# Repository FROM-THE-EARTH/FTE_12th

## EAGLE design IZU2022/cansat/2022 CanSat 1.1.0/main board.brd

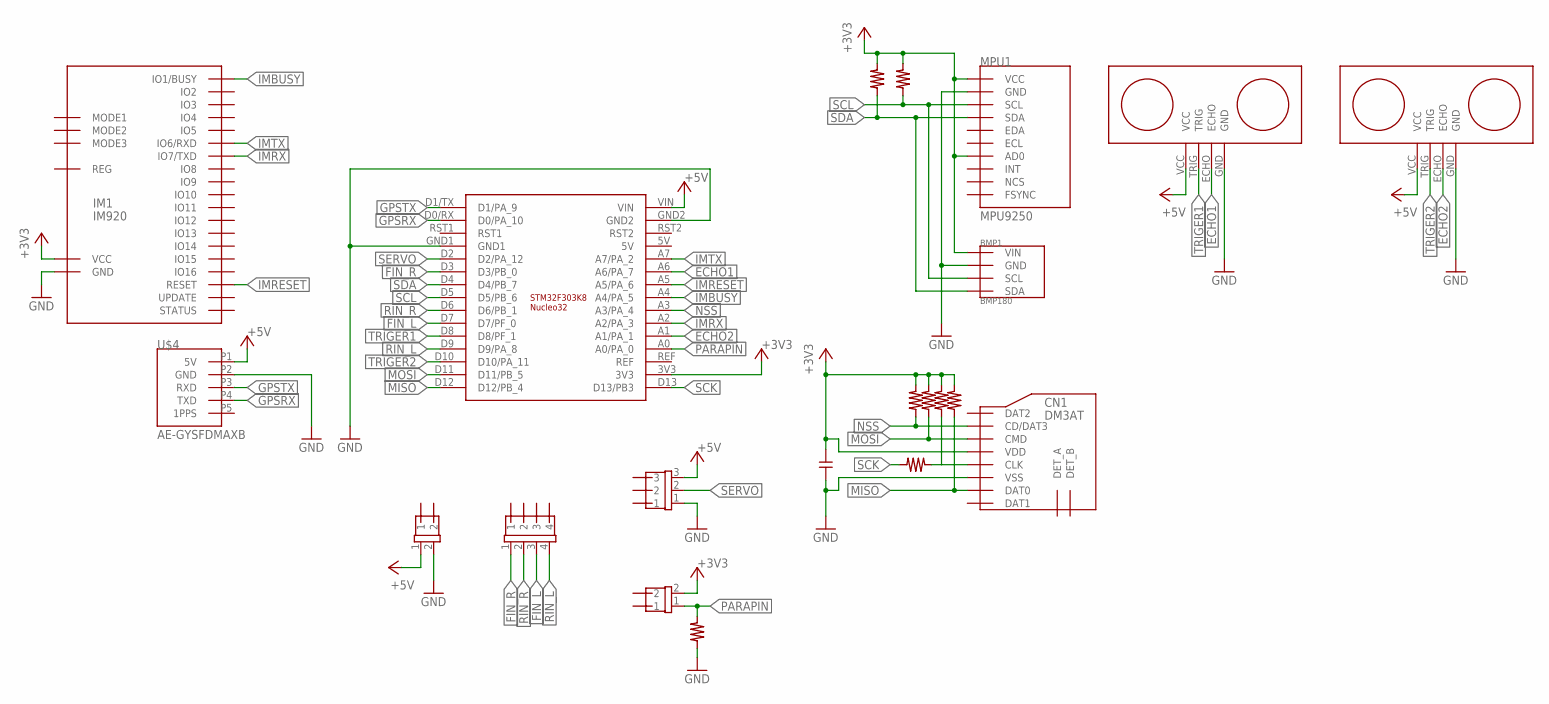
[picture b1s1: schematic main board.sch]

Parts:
BMP1: BMP180; GY-68
C4: CAPACITOR-CERAMICC_1
CN1: DM3AT
CONN1, CONN2: 2PIN
CONN3: 4PIN
CONN4: 3PIN
CP1: STM32F303K8-NUCLEO32; STM32-NUCLEO32
EC1, EC2: ECHO
IM1: IM920
MPU1: MPU9250; GY-9250
R2, R4, R5, R6, R7, R8, R9, R10: RESISTER; REGISTER
U$4: AE-GYSFDMAXB

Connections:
+3V3: BMP1.P1 (VIN), C4.2, CN1.VDD, CONN1.2, CP1.3V3, IM1.IO23 (VCC), MPU1.P1 (VCC), MPU1.P7 (AD0), R4.B, R5.B, R6.B, R7.B, R8.B, R9.B
+5V: CONN2.1, CONN4.3, CP1.VIN, EC1.VCC, EC2.VCC, U$4.P1 (5V)
ECHO1: CP1.A6 (A6/PA_7), EC1.ECHO
ECHO2: CP1.A1 (A1/PA_1), EC2.ECHO
FIN_L: CONN3.3, CP1.D7 (D7/PF_0)
FIN_R: CONN3.1, CP1.D3 (D3/PB_0)
GND: BMP1.P2 (GND), C4.1, CN1.VSS, CONN2.2, CONN4.1, CP1.GND1, CP1.GND2, EC1.GND, EC2.GND, IM1.IO24 (GND), MPU1.P2 (GND), R2.A, U$4.P2 (GND)
GPSRX: CP1.D0/RX (D0/PA_10), U$4.P4 (TXD)
GPSTX: CP1.D1/TX (D1/PA_9), U$4.P3 (RXD)
IMBUSY: CP1.A4 (A4/PA_5), IM1.IO1 (IO1/BUSY)
IMRESET: CP1.A5 (A5/PA_6), IM1.IO25 (RESET)
IMRX: CP1.A2 (A2/PA_3), IM1.IO7 (IO7/TXD)
IMTX: CP1.A7 (A7/PA_2), IM1.IO6 (IO6/RXD)
MISO: CN1.DAT0, CP1.D12 (D12/PB_4), R6.A
MOSI: CN1.CMD, CP1.D11 (D11/PB_5), R8.A
unnamed: CN1.CLK, R7.A, R10.B
NSS: CN1.CD/DAT3, CP1.A3 (A3/PA_4), R9.A
PARAPIN: CONN1.1, CP1.A0 (A0/PA_0), R2.B
RIN_L: CONN3.4, CP1.D9 (D9/PA_8)
RIN_R: CONN3.2, CP1.D6 (D6/PB_1)
SCK: CP1.D13 (D13/PB3), R10.A
SCL: BMP1.P3 (SCL), CP1.D5 (D5/PB_6), MPU1.P3 (SCL), R4.A
SDA: BMP1.P4 (SDA), CP1.D4 (D4/PB_7), MPU1.P4 (SDA), R5.A
SERVO: CONN4.2, CP1.D2 (D2/PA_12)
TRIGER1: CP1.D8 (D8/PF_1), EC1.TRIG
TRIGER2: CP1.D10 (D10/PA_11), EC2.TRIG

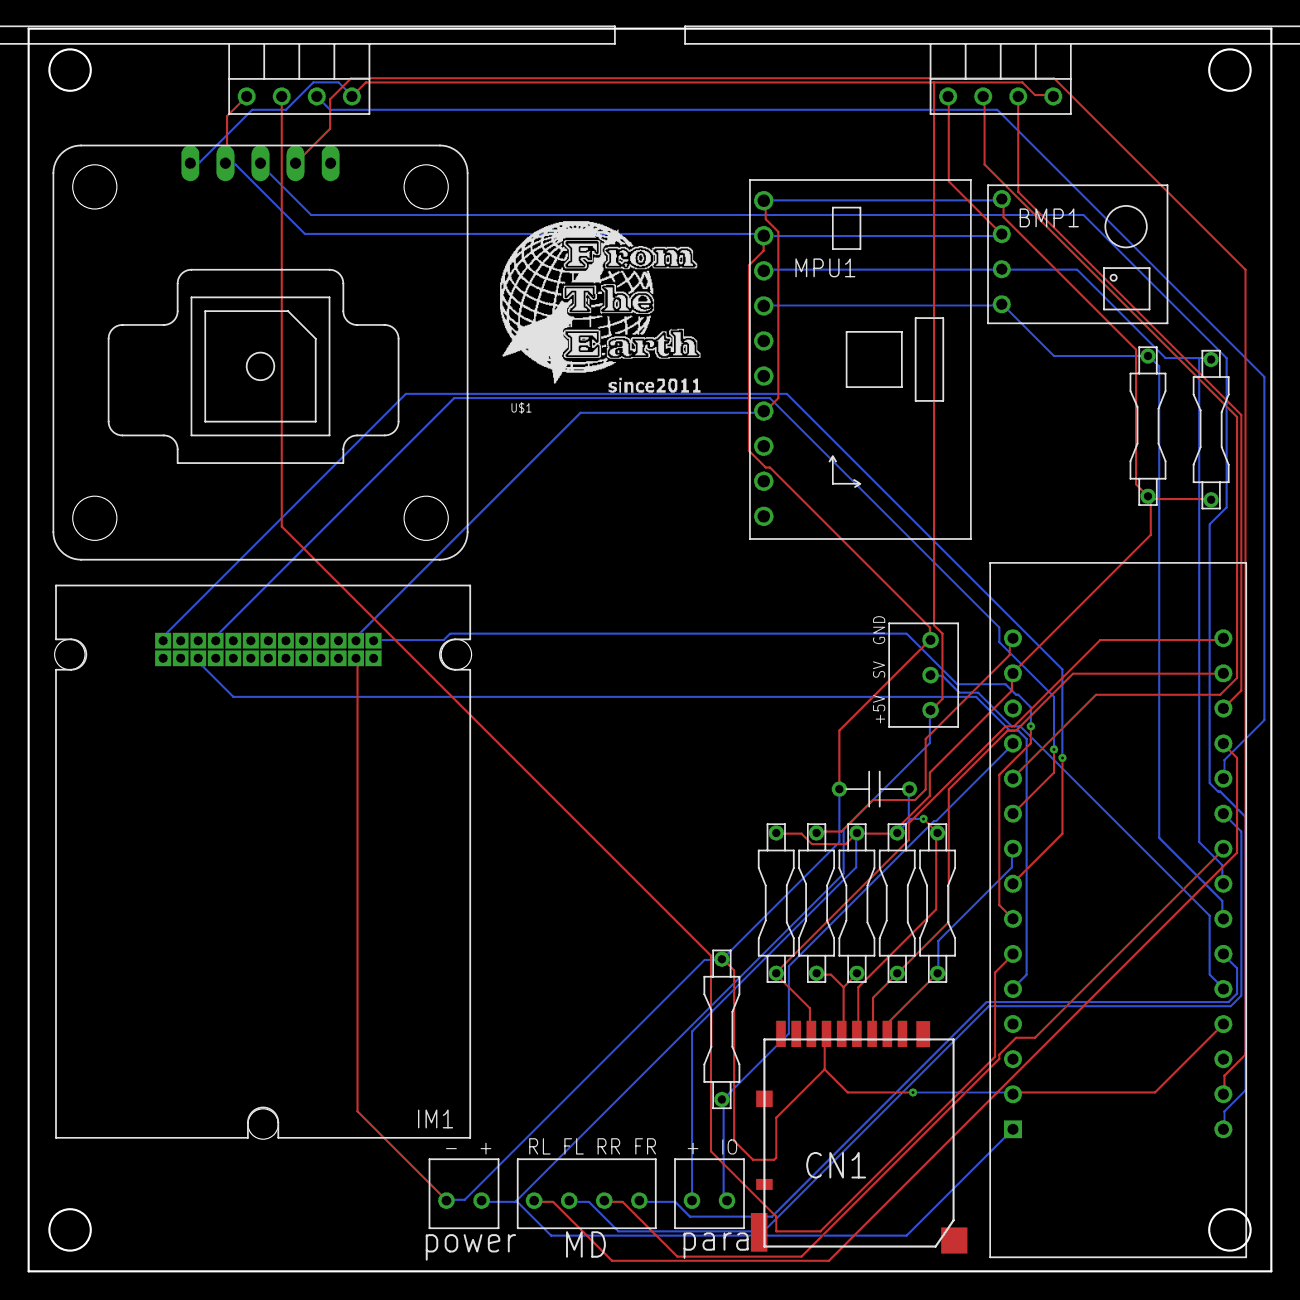
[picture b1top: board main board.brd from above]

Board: 2 copper layers, 90.0 x 90.0 mm, 22 parts (0 on the bottom side), 26 nets.

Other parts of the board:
U$1: LOGO

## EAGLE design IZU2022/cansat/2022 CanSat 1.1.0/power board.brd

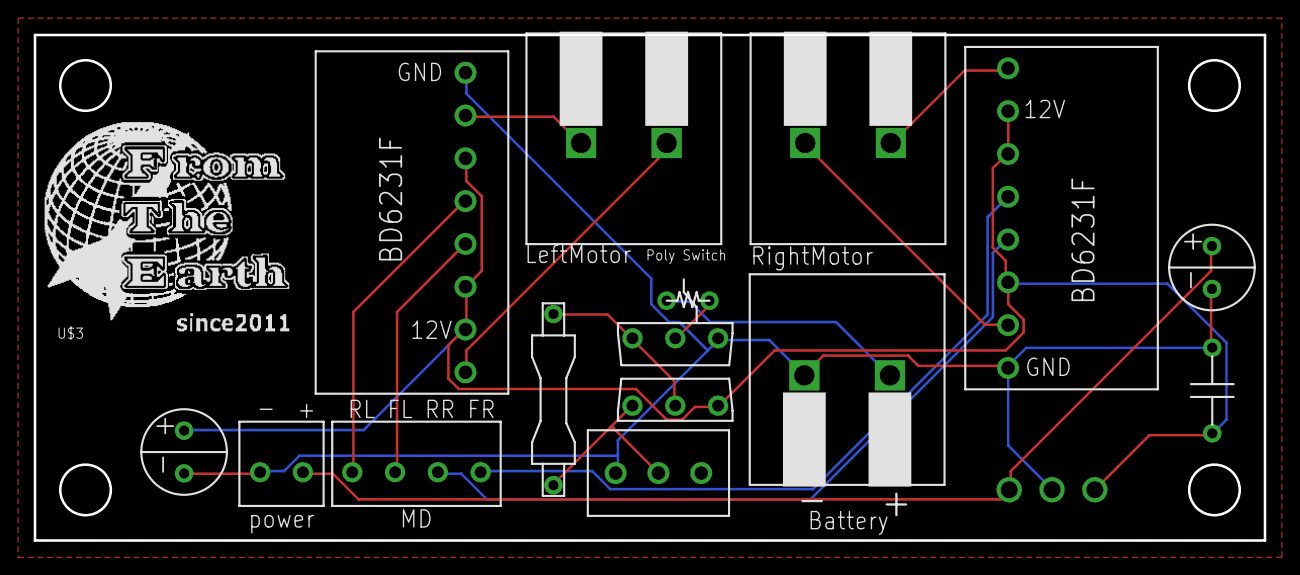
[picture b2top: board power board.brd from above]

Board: 2 copper layers, 73.0 x 30.0 mm, 17 parts (1 on the bottom side), 15 nets.

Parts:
C1, C3: CAPACITOR-ELECTROLYTIC_1
C2: CAPACITOR-CERAMICC_1
CONN1: 2PIN
CONN2: 4PIN
M78AR033-1: M78AR033-1
MD1, MD2: BD6231F_DIP_1
PS1: ~1.0A; POLYSWITCH
R1: 100K; REGISTER
SW1: SLIDE-SW
TM1, TM2, TM3: TERMINAL_SLOPED_2PIN
U$1, U$2: 2SJ681-PCH; 2SJ681
U$3: LOGO

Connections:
+5V: C1.KS, CONN1.1, M78AR033-1.VOUT
+12V: C2.1, C3.KS, M78AR033-1.VIN, MD1.VCC1, MD1.VCC2, MD1.VREF, MD2.VCC1, MD2.VCC2, MD2.VREF, U$2.SOURCE
FIN_L: CONN2.3, MD2.FIN
FIN_R: CONN2.1, MD1.FIN
GND: C1.AN, C2.2, C3.AN, CONN1.2, M78AR033-1.GND, MD1.GND, MD2.GND, SW1.RIGHT, TM3.2, U$1.GATE
unnamed: PS1.2, U$1.DRAIN
unnamed: R1.B, U$1.SOURCE, U$2.DRAIN
unnamed: R1.A, SW1.CENTER, U$2.GATE
unnamed: PS1.1, TM3.1
OUT1_L: MD2.OUT1, TM1.2
OUT1_R: MD1.OUT1, TM2.2
OUT2_L: MD2.OUT2, TM1.1
OUT2_R: MD1.OUT2, TM2.1
RIN_L: CONN2.4, MD2.RIN
RIN_R: CONN2.2, MD1.RIN

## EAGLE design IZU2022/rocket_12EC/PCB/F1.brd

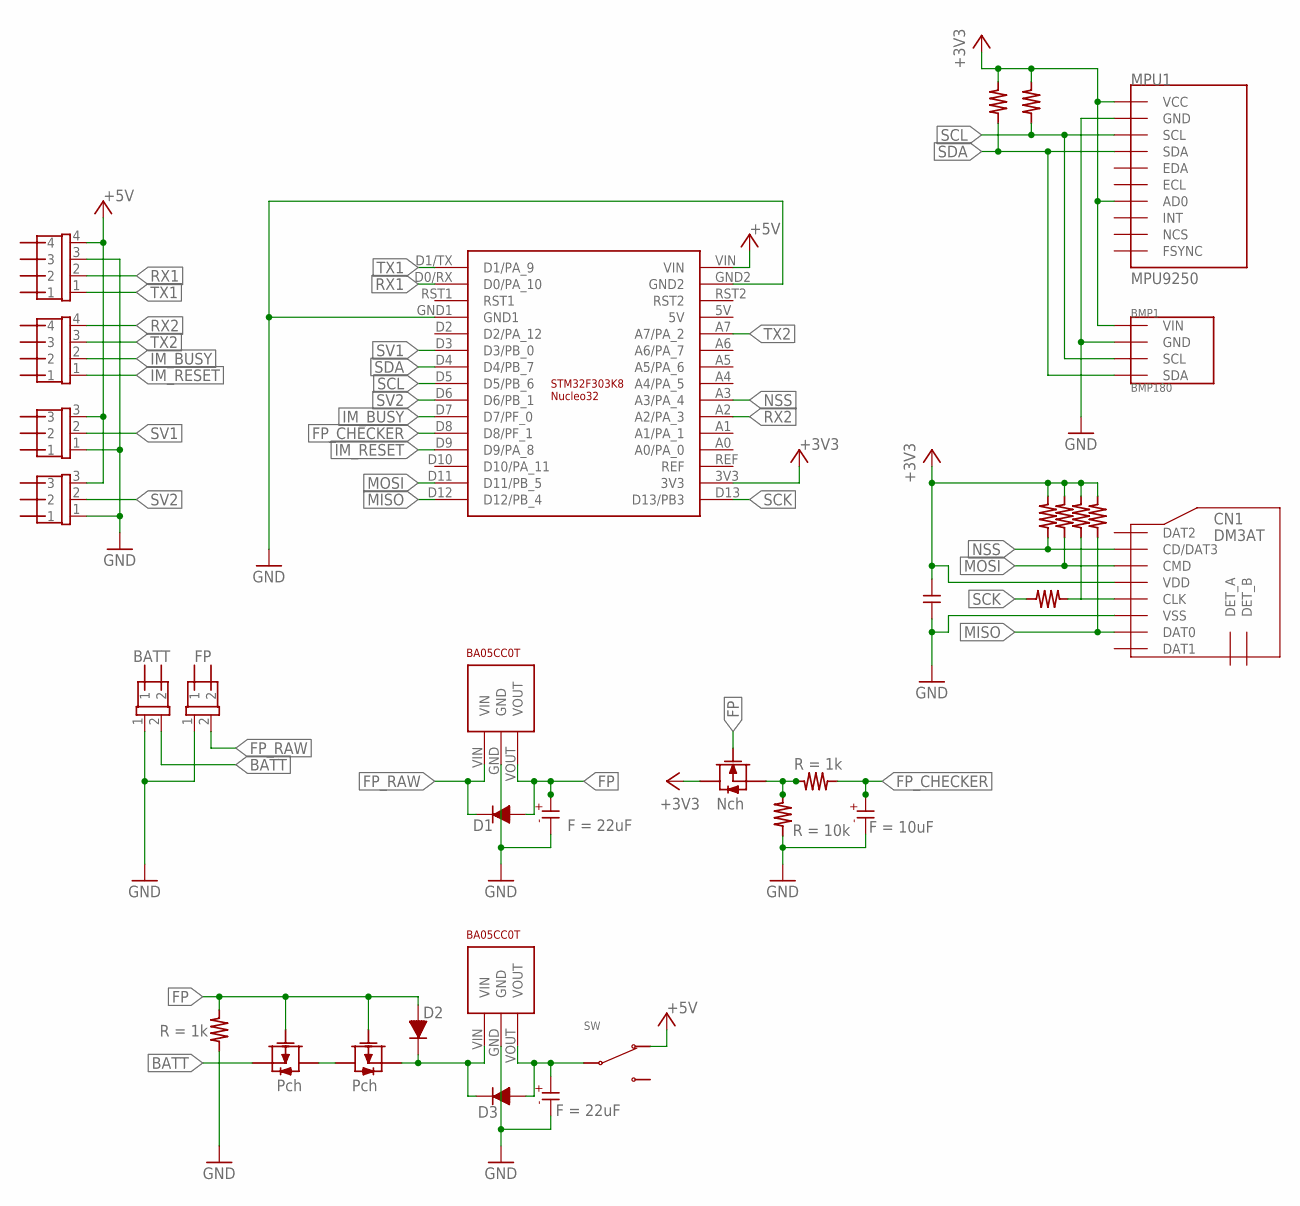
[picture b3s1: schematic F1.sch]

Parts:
BATT: 2PIN
BMP1: BMP180; GY-68
C1: 22uF; CAPACITOR-ELECTROLYTIC_1
C2, C3: CAPACITOR-ELECTROLYTIC_1
C4: CAPACITOR-CERAMICC_1
CN1: DM3AT
CONN1, CONN2: 4PIN
CONN3, CONN4: 3PIN
CP1: STM32F303K8-NUCLEO32; STM32-NUCLEO32
D1: DIODE
FRIGHT-PIN: 2PIN
MPU1: MPU9250; GY-9250
R1, R2, R3, R4, R5, R6, R7, R8, R9, R10: RESISTER; REGISTER
REG1, REG2: BA05CC0T
SW1: SLIDE-SW_1; SLIDE-SW
U$1, U$4: DIODE
U$2, U$3: 2SJ681-PCH; 2SJ681
U$5: 2SK4017-NCH; 2SK4017

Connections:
+3V3: BMP1.P1 (VIN), C4.2, CN1.VDD, CP1.3V3, MPU1.P1 (VCC), MPU1.P7 (AD0), R4.B, R5.B, R6.B, R7.B, R8.B, R9.B, U$5.DRAIN
+5V: CONN1.4, CONN3.3, CONN4.3, CP1.VIN, SW1.LEFT
BATT: BATT.2, U$2.SOURCE
FP: C1.KS, D1.A (ANODE), R1.B, REG1.VOUT, U$1.A (ANODE), U$2.GATE, U$3.GATE, U$5.GATE
FP_CHECKER: C3.KS, CP1.D8 (D8/PF_1), R3.A
FP_RAW: D1.K (KASODE), FRIGHT-PIN.2, REG1.VIN
GND: BATT.1, BMP1.P2 (GND), C1.AN, C2.AN, C3.AN, C4.1, CN1.VSS, CONN1.3, CONN3.1, CONN4.1, CP1.GND1, CP1.GND2, FRIGHT-PIN.1, MPU1.P2 (GND), R1.A, R2.A, REG1.GND, REG2.GND
IM_BUSY: CONN2.2, CP1.D7 (D7/PF_0)
IM_RESET: CONN2.1, CP1.D9 (D9/PA_8)
MISO: CN1.DAT0, CP1.D12 (D12/PB_4), R6.A
MOSI: CN1.CMD, CP1.D11 (D11/PB_5), R8.A
unnamed: U$2.DRAIN, U$3.DRAIN
unnamed: REG2.VIN, U$1.K (KASODE), U$3.SOURCE, U$4.K (KASODE)
unnamed: C2.KS, REG2.VOUT, SW1.CENTER, U$4.A (ANODE)
unnamed: R2.B, R3.B, U$5.SOURCE
unnamed: CN1.CLK, R7.A, R10.B
NSS: CN1.CD/DAT3, CP1.A3 (A3/PA_4), R9.A
RX1: CONN1.2, CP1.D0/RX (D0/PA_10)
RX2: CONN2.4, CP1.A2 (A2/PA_3)
SCK: CP1.D13 (D13/PB3), R10.A
SCL: BMP1.P3 (SCL), CP1.D5 (D5/PB_6), MPU1.P3 (SCL), R4.A
SDA: BMP1.P4 (SDA), CP1.D4 (D4/PB_7), MPU1.P4 (SDA), R5.A
SV1: CONN3.2, CP1.D3 (D3/PB_0)
SV2: CONN4.2, CP1.D6 (D6/PB_1)
TX1: CONN1.1, CP1.D1/TX (D1/PA_9)
TX2: CONN2.3, CP1.A7 (A7/PA_2)

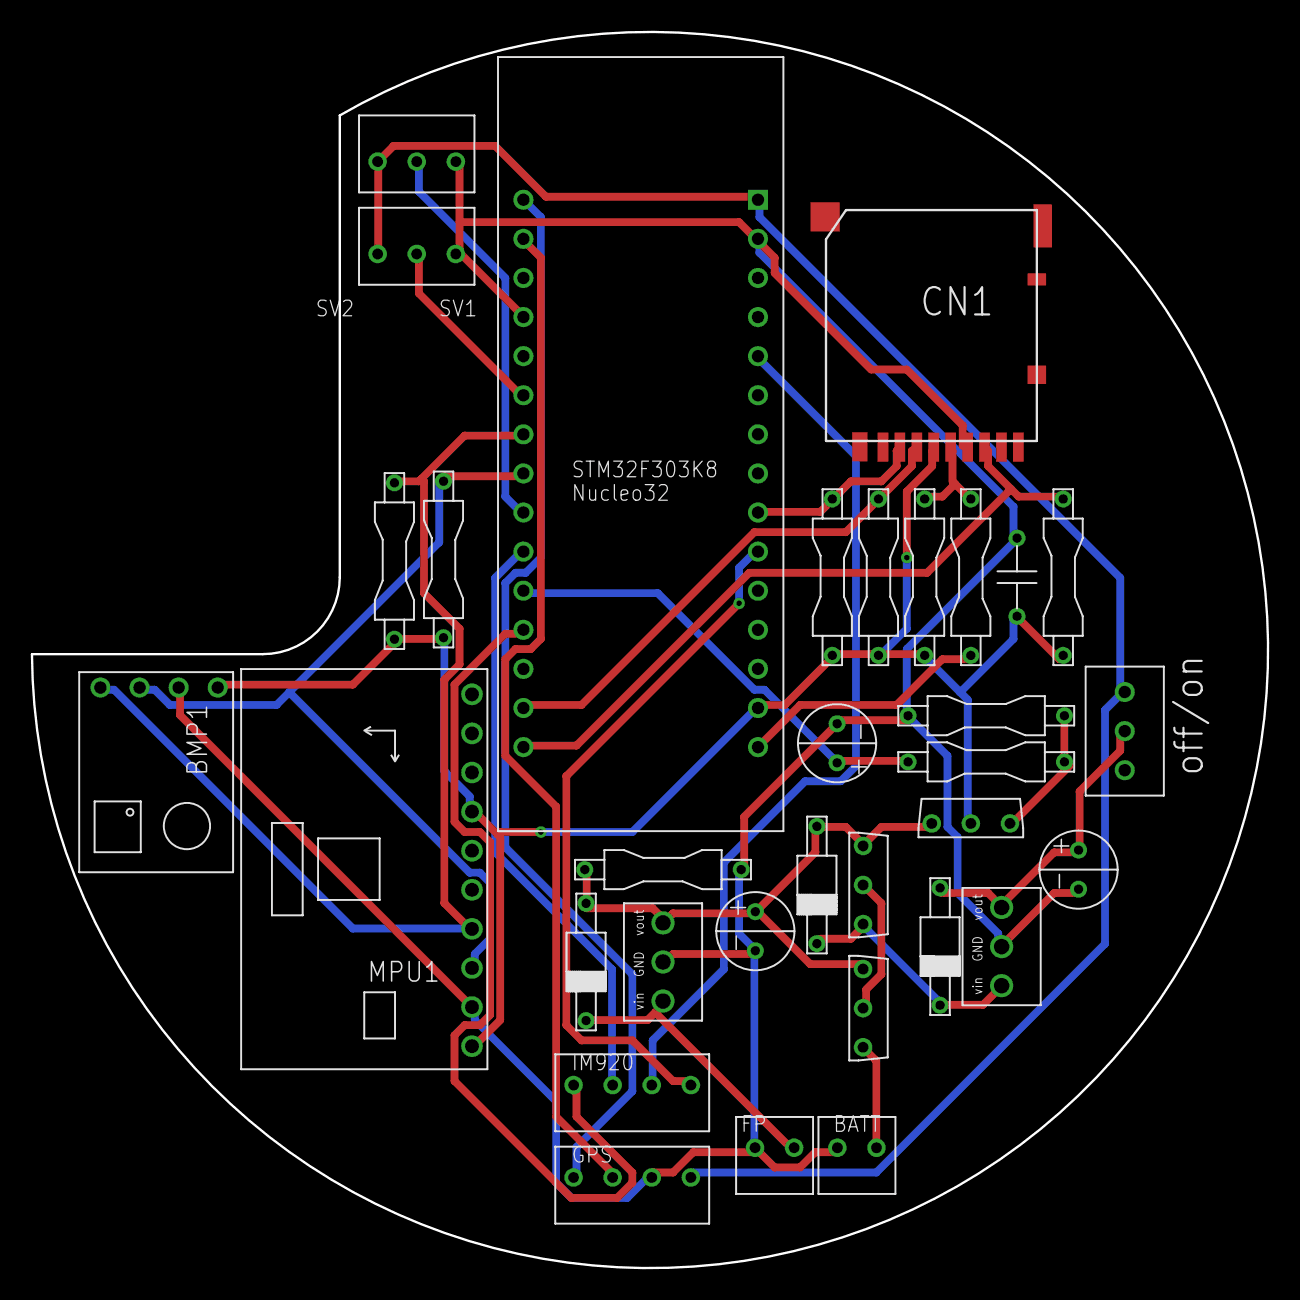
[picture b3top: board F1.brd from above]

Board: 2 copper layers, 80.3 x 80.3 mm, 33 parts (0 on the bottom side), 26 nets.

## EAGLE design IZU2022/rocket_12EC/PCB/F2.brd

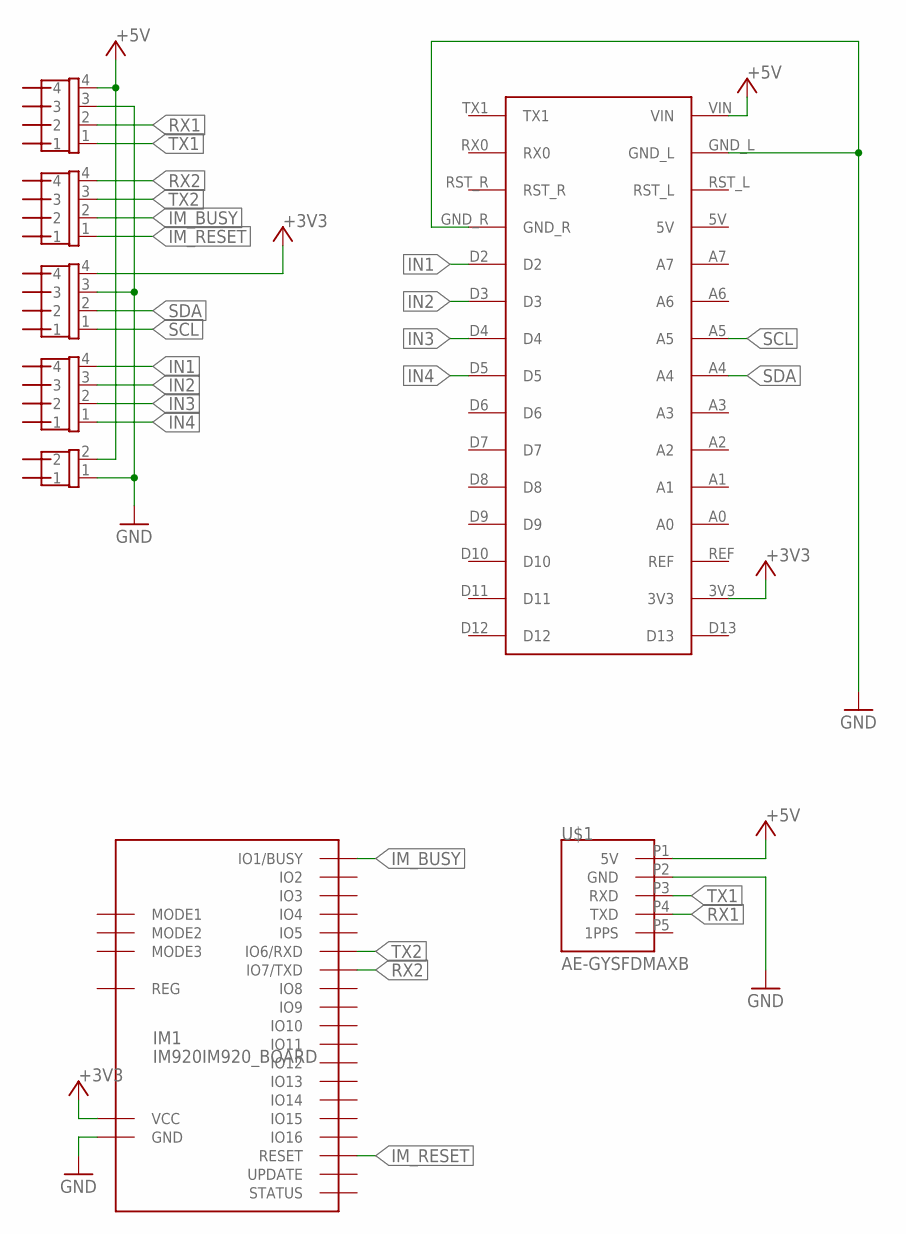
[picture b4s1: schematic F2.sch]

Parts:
ARDUINO_NANO2: ARDUINO_NANO
CONN1, CONN2, CONN3, CONN4: 4PIN
CONN5: 2PIN
IM1: IM920IM920_BOARD; IM920_BOARD
U$1: AE-GYSFDMAXB

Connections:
+3V3: ARDUINO_NANO2.3V3, CONN3.4, IM1.IO23 (VCC)
+5V: ARDUINO_NANO2.VIN, CONN1.4, CONN5.2, U$1.P1 (5V)
GND: ARDUINO_NANO2.GND_L, ARDUINO_NANO2.GND_R, CONN1.3, CONN3.3, CONN5.1, IM1.IO24 (GND), U$1.P2 (GND)
IM_BUSY: CONN2.2, IM1.IO1 (IO1/BUSY)
IM_RESET: CONN2.1, IM1.IO25 (RESET)
IN1: ARDUINO_NANO2.D2, CONN4.4
IN2: ARDUINO_NANO2.D3, CONN4.3
IN3: ARDUINO_NANO2.D4, CONN4.2
IN4: ARDUINO_NANO2.D5, CONN4.1
RX1: CONN1.2, U$1.P4 (TXD)
RX2: CONN2.4, IM1.IO7 (IO7/TXD)
SCL: ARDUINO_NANO2.A5, CONN3.1
SDA: ARDUINO_NANO2.A4, CONN3.2
TX1: CONN1.1, U$1.P3 (RXD)
TX2: CONN2.3, IM1.IO6 (IO6/RXD)

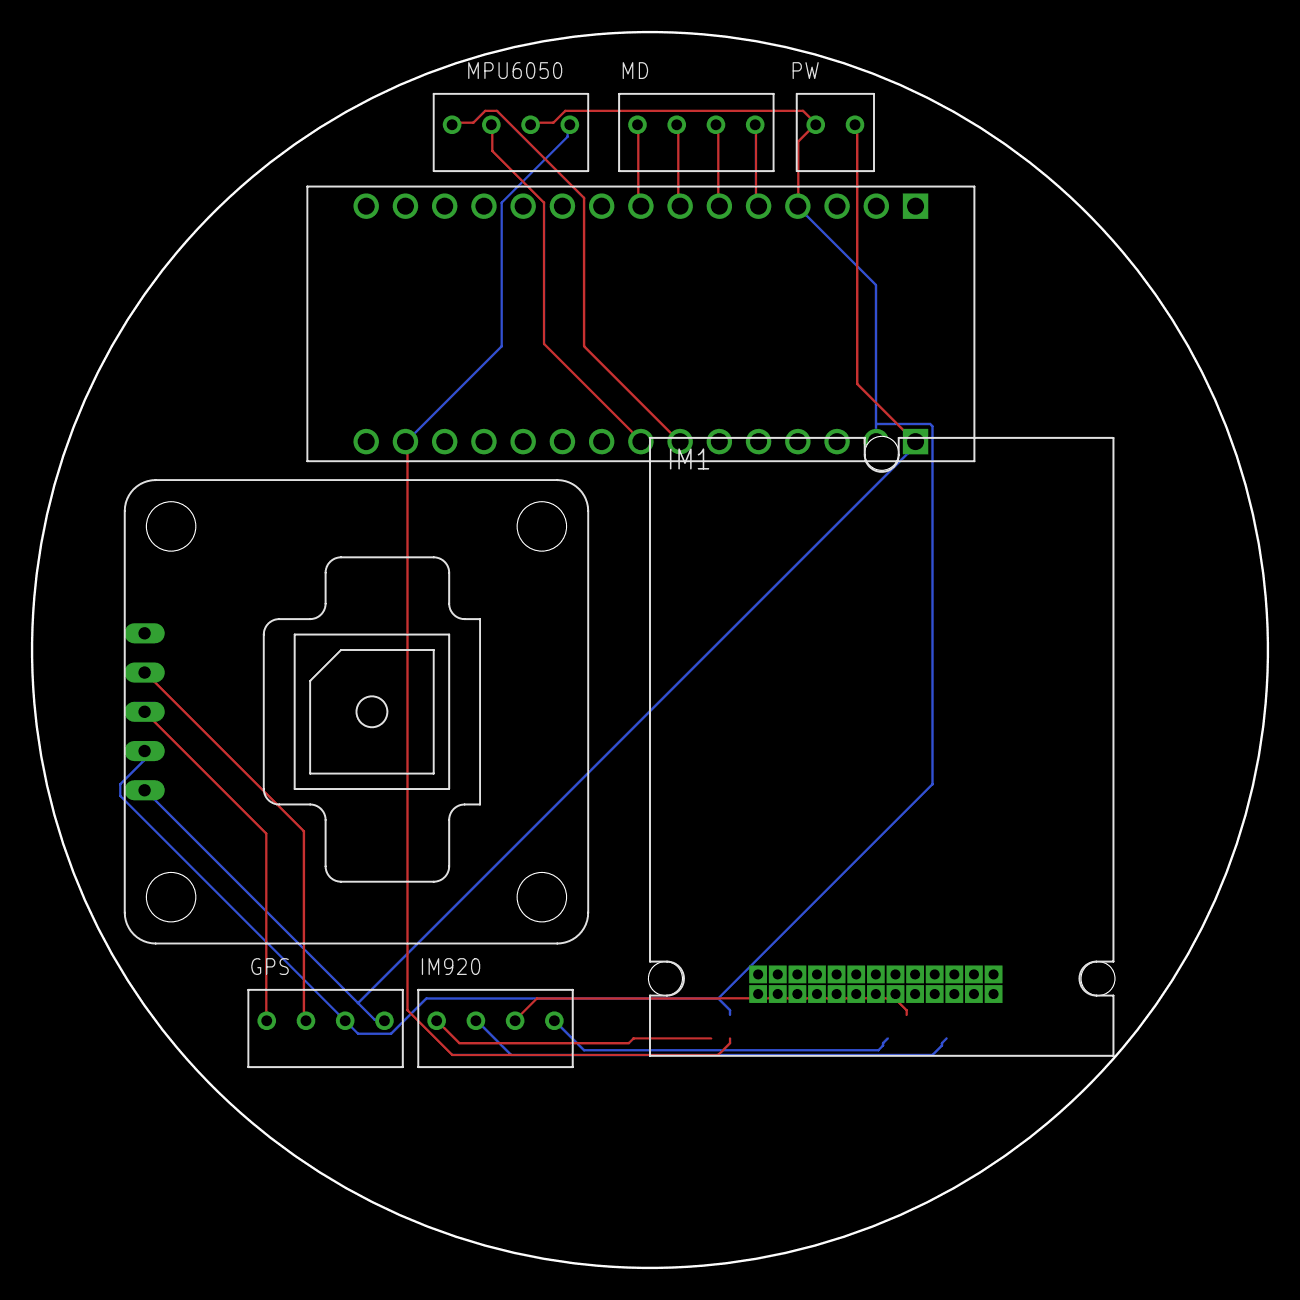
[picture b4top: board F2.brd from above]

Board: 2 copper layers, 80.0 x 80.0 mm, 8 parts (0 on the bottom side), 15 nets.

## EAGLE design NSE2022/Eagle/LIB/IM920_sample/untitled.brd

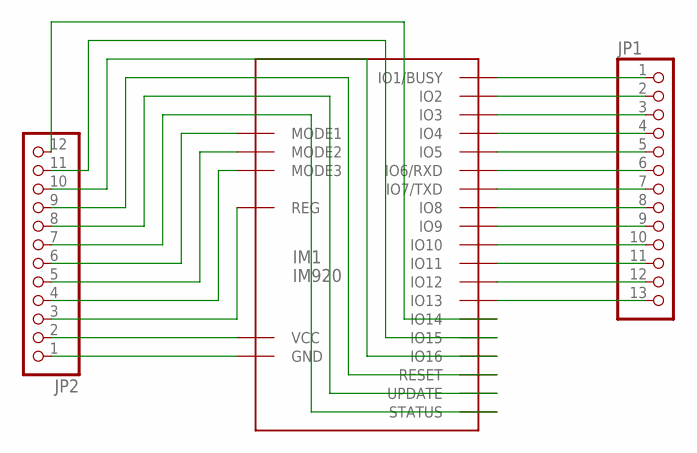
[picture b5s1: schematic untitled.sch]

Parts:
IM1: IM920
JP1: PINHD-1X13; 1X13
JP2: PINHD-1X12; 1X12

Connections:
1PIN: IM1.IO25 (RESET), JP2.9
unnamed: IM1.IO1 (IO1/BUSY), JP1.1
unnamed: IM1.IO2, JP1.2
unnamed: IM1.IO3, JP1.3
unnamed: IM1.IO4, JP1.4
unnamed: IM1.IO5, JP1.5
unnamed: IM1.IO6 (IO6/RXD), JP1.6
unnamed: IM1.IO7 (IO7/TXD), JP1.7
unnamed: IM1.IO8, JP1.8
unnamed: IM1.IO9, JP1.9
unnamed: IM1.IO10, JP1.10
unnamed: IM1.IO11, JP1.11
unnamed: IM1.IO12, JP1.12
unnamed: IM1.IO24 (GND), JP2.1
unnamed: IM1.IO23 (VCC), JP2.2
unnamed: IM1.IO22 (REG), JP2.3
unnamed: IM1.IO19 (MODE3), JP2.4
unnamed: IM1.IO18 (MODE2), JP2.5
unnamed: IM1.IO17 (MODE1), JP2.6
unnamed: IM1.IO21 (STATUS), JP2.7
unnamed: IM1.IO20 (UPDATE), JP2.8
unnamed: IM1.IO16, JP2.10
unnamed: IM1.IO15, JP2.11
unnamed: IM1.IO14, JP2.12
unnamed: IM1.IO13, JP1.13

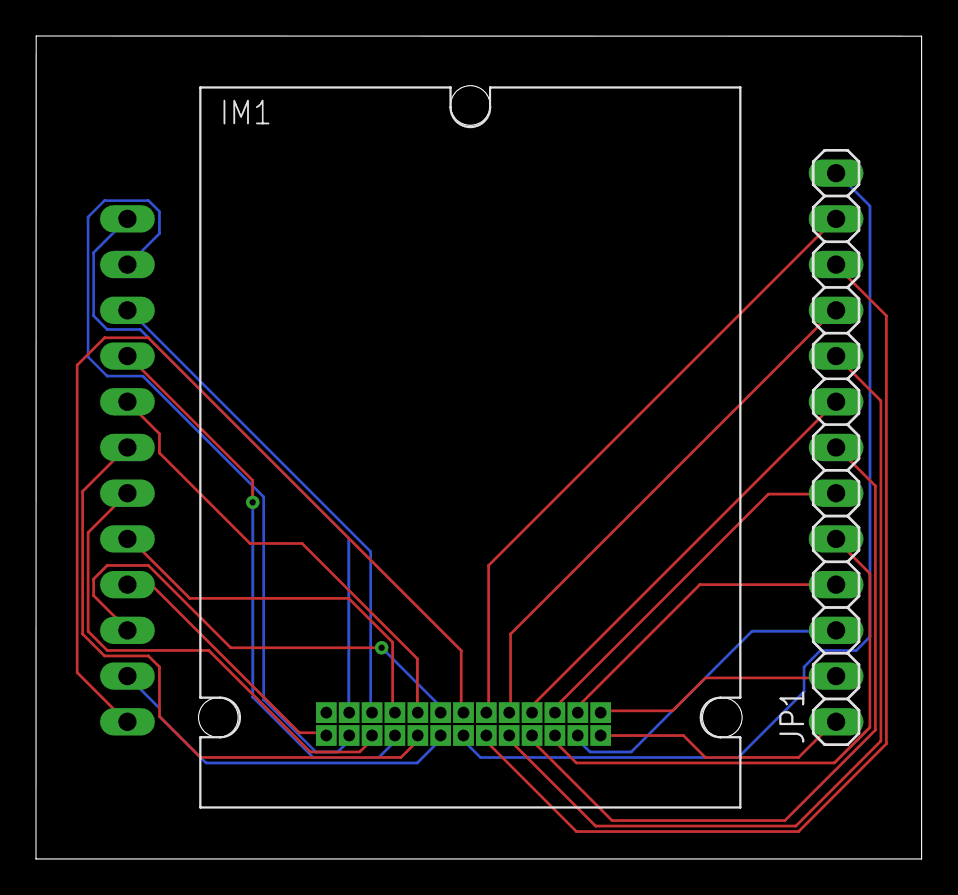
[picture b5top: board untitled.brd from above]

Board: 2 copper layers, 49.2 x 45.7 mm, 3 parts (1 on the bottom side), 25 nets.

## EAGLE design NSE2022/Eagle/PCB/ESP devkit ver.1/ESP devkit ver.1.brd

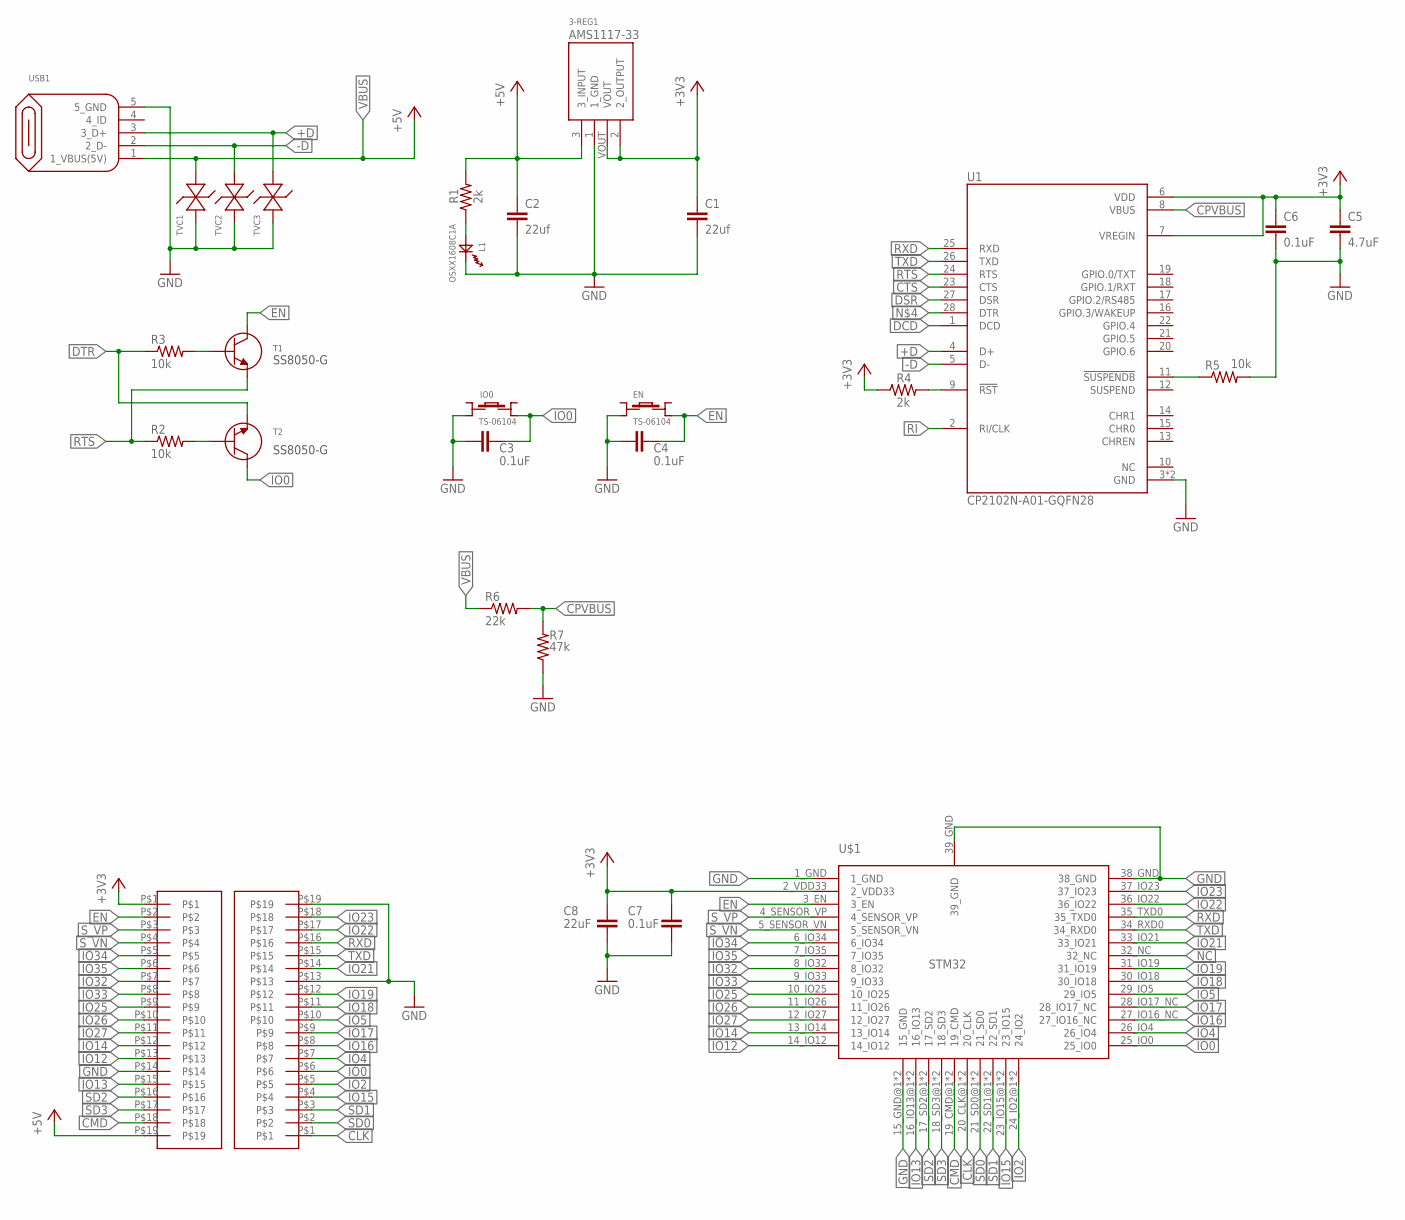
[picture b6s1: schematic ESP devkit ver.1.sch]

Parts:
3-REG1: AZ1117CH-3.3TRG1
C1, C2: 22uf; C0603
C3, C4, C6, C7: 0.1uF; C0603
C5: 4.7uF; C0402
C8: 22uF; C0603
EN: TS-06104
IO0: TS-06104
L1: OSXX1608C1A
R1, R4: 2k; R0201
R2, R3, R5: 10k; R0201
R6: 22k; R0201
R7: 47k; R0201
T1, T2: NPN_SS8050-G
TVC1, TVC2, TVC3: ESD5484FCT5G
U1: CP2102N-A01-GQFN28; QFN50P500X500X80-29N
U$1: ESP32-WROOM&WROVER; ESP32-WROVER&WROOM
U$4, U$5: 19_2.54
USB1: MICRO-B_ZX62R-B-5P

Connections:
+3V3: 3-REG1.2 (2_OUTPUT), 3-REG1.VOUT, C1.1, C5.1, C6.1, C7.1, C8.1, R4.1, U1.6 (VDD), U1.7 (VREGIN), U$1.2_VDD33, U$4.P$1
+5V: 3-REG1.3 (3_INPUT), C2.1, R1.2, U$4.P$19
+D: TVC3.2_AN, U1.4 (D+), USB1.3 (3_D+)
-D: TVC2.2_AN, U1.5 (D-), USB1.2 (2_D-)
CLK: U$1.20_CLK@1 (20_CLK), U$1.20_CLK@2 (20_CLK), U$5.P$1
CMD: U$1.19_CMD@1 (19_CMD), U$1.19_CMD@2 (19_CMD), U$4.P$18
CPVBUS: R6.2, R7.2, U1.8 (VBUS)
CTS: U1.23 (CTS)
DCD: U1.1 (DCD)
DSR: U1.27 (DSR)
DTR: R3.1, T2.2
EN: C4.1, EN.D, T1.3, U$1.3_EN, U$4.P$2
GND: 3-REG1.1 (1_GND), C1.2, C2.2, C3.2, C4.2, C5.2, C6.2, C7.2, C8.2, EN.B, IO0.B, L1.CT, R5.2, R7.1, TVC1.1_CT, TVC2.1_CT, TVC3.1_CT, U1.3 (GND), U1.29 (GND), U$1.1_GND, U$1.15_GND@1 (15_GND), U$1.15_GND@2 (15_GND), U$1.38_GND, U$1.39_GND, U$4.P$14, U$5.P$13, U$5.P$19, USB1.5 (5_GND)
IO0: C3.1, IO0.D, T2.3, U$1.25_IO0, U$5.P$6
IO2: U$1.24_IO2@1 (24_IO2), U$1.24_IO2@2 (24_IO2), U$5.P$5
IO4: U$1.26_IO4, U$5.P$7
IO5: U$1.29_IO5, U$5.P$10
IO12: U$1.14_IO12, U$4.P$13
IO13: U$1.16_IO13@1 (16_IO13), U$1.16_IO13@2 (16_IO13), U$4.P$15
IO14: U$1.13_IO14, U$4.P$12
IO15: U$1.23_IO15@1 (23_IO15), U$1.23_IO15@2 (23_IO15), U$5.P$4
IO16: U$1.27_IO16_NC, U$5.P$8
IO17: U$1.28_IO17_NC, U$5.P$9
IO18: U$1.30_IO18, U$5.P$11
IO19: U$1.31_IO19, U$5.P$12
IO21: U$1.33_IO21, U$5.P$14
IO22: U$1.36_IO22, U$5.P$17
IO23: U$1.37_IO23, U$5.P$18
IO25: U$1.10_IO25, U$4.P$9
IO26: U$1.11_IO26, U$4.P$10
IO27: U$1.12_IO27, U$4.P$11
IO32: U$1.8_IO32, U$4.P$7
IO33: U$1.9_IO33, U$4.P$8
IO34: U$1.6_IO34, U$4.P$5
IO35: U$1.7_IO35, U$4.P$6
unnamed: L1.AN, R1.1
unnamed: R3.2, T1.1
unnamed: R2.2, T2.1
unnamed: R4.2, U1.9 (!RST)
unnamed: R5.1, U1.11 (!SUSPENDB)
NC: U$1.32_NC
RI: U1.2 (RI/CLK)
RTS: R2.1, T1.2, U1.24 (RTS)
RXD: U1.25 (RXD), U$1.35_TXD0, U$5.P$16
SD0: U$1.21_SD0@1 (21_SD0), U$1.21_SD0@2 (21_SD0), U$5.P$2
SD1: U$1.22_SD1@1 (22_SD1), U$1.22_SD1@2 (22_SD1), U$5.P$3
SD2: U$1.17_SD2@1 (17_SD2), U$1.17_SD2@2 (17_SD2), U$4.P$16
SD3: U$1.18_SD3@1 (18_SD3), U$1.18_SD3@2 (18_SD3), U$4.P$17
S_VN: U$1.5_SENSOR_VN, U$4.P$4
S_VP: U$1.4_SENSOR_VP, U$4.P$3
TXD: U1.26 (TXD), U$1.34_RXD0, U$5.P$15
VBUS: R6.1, TVC1.2_AN, USB1.1 (1_VBUS(5V))

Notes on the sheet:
SS8050-G

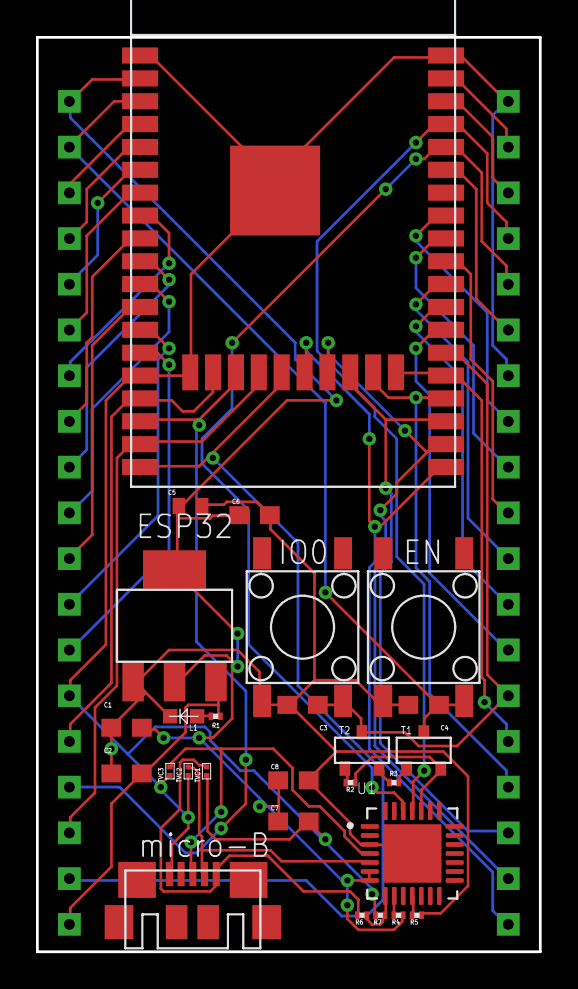
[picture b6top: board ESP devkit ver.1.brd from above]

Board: 2 copper layers, 27.9 x 50.8 mm, 29 parts (0 on the bottom side), 47 nets.

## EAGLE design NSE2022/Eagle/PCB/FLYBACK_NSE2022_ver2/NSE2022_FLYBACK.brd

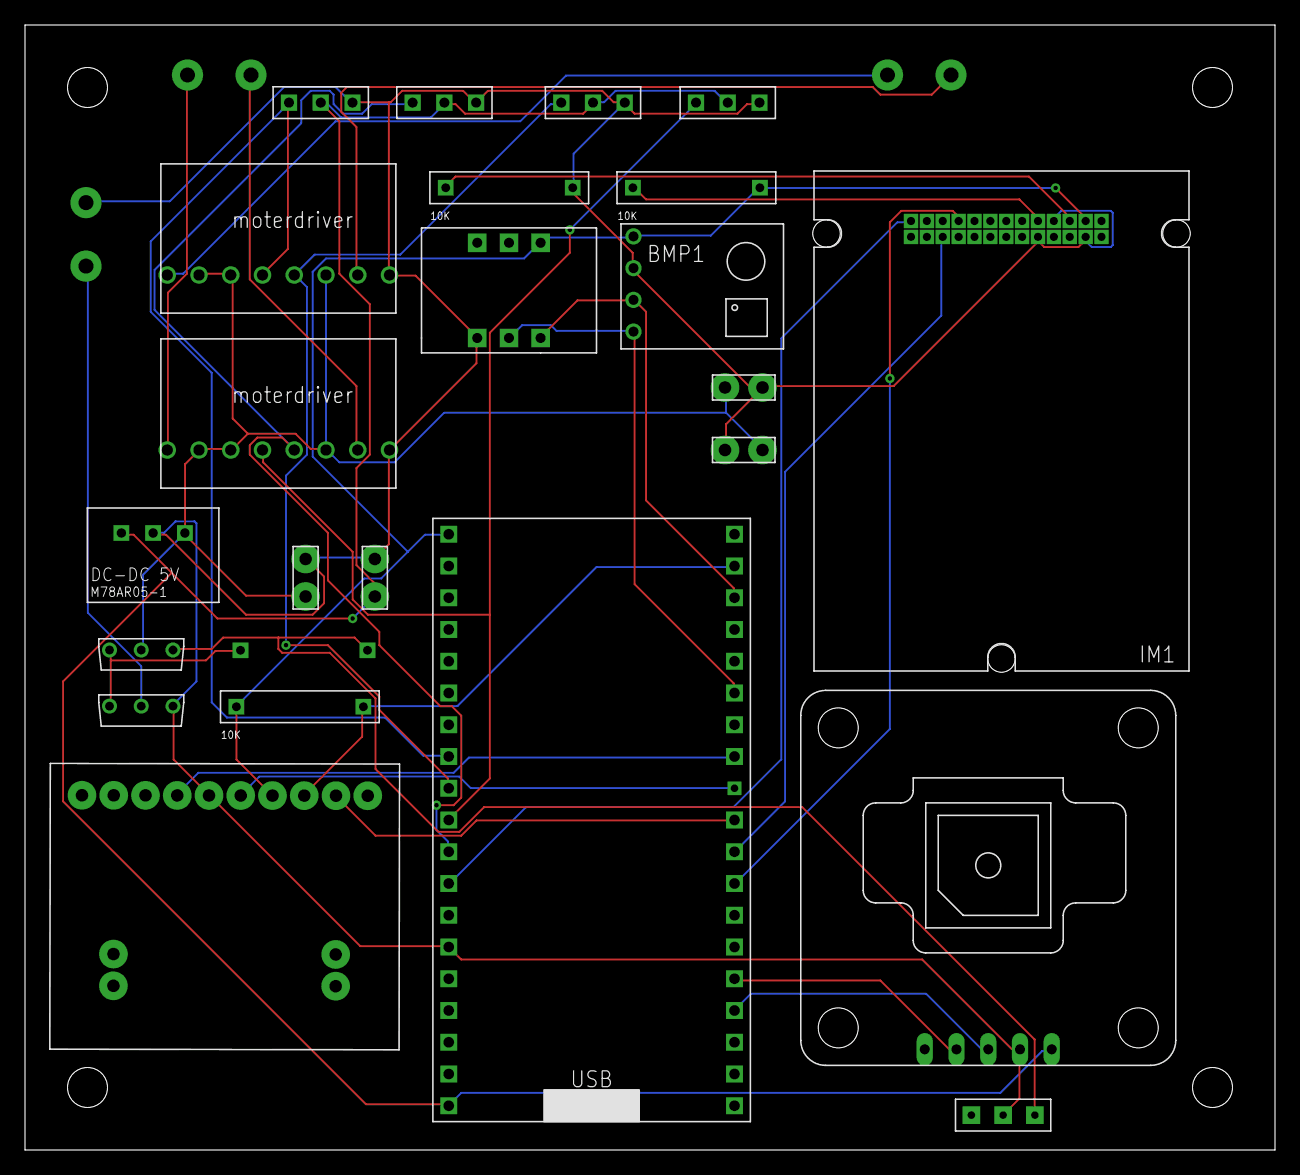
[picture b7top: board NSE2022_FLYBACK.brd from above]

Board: 2 copper layers, 100.0 x 90.0 mm, 27 parts (1 on the bottom side), 28 nets.

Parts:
BMP1: BMP180; GY-68
BMX1: BMX055
CERAMIC_CAPACITOR1, CERAMIC_CAPACITOR2, CERAMIC_CAPACITOR3, CERAMIC_CAPACITOR4: CERAMIC_CAPACITOR
CONNECTION1: SD_SOCKET; SD
CONNECTOR1, CONNECTOR2, CONNECTOR3: 2PIN
IM1: IM920
U$1, U$5: 2SJ681-PCH; 2SJ681
U$2, U$9, U$10, U$11: MG996R
U$3: AE-GYSFDMAXB
U$4: ESP32
U$6: M78AR05-1
U$7, U$12, U$13, U$14: KATORESISTOR
U$8: SLIDESWITCH
U$15, U$16: MOTORDRIVER

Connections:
+3V3: BMP1.P1, BMX1.3V3, CONNECTION1.3.3V, IM1.IO23, U$4.3.3V, U$12.E, U$14.R
+5V: CERAMIC_CAPACITOR1.P$1, U$2.5V, U$3.P1, U$4.5V, U$6.VOUT, U$9.5V, U$10.5V, U$11.5V
+12V: CERAMIC_CAPACITOR2.P$1, CERAMIC_CAPACITOR3.P$2, CERAMIC_CAPACITOR4.P$2, U$5.DRAIN, U$6.VIN, U$15.VCC1, U$15.VCC2, U$15.VREF, U$16.VCC1, U$16.VCC2, U$16.VREF
GND: BMP1.P2, BMX1.GND, CERAMIC_CAPACITOR1.P$2, CERAMIC_CAPACITOR2.P$2, CERAMIC_CAPACITOR3.P$1, CERAMIC_CAPACITOR4.P$1, CONNECTION1.GND, CONNECTOR2.2, IM1.IO18, IM1.IO19, IM1.IO24, U$1.GATE, U$2.GND, U$3.P2, U$4.GND1, U$6.GND, U$8.C, U$9.GND, U$10.GND, U$11.GND, U$13.E, U$15.GND, U$16.GND
GPSRX: U$3.P4, U$4.GPIO2
GPSTX: U$3.P3, U$4.GPIO15
IMBUSY: IM1.IO1, U$4.GPIO14
IMRX: IM1.IO7, U$4.GPIO16
IMTX: IM1.IO6, U$4.GPIO17
LF: CONNECTOR3.1, U$16.OUT1
LR: CONNECTOR3.2, U$16.OUT2
MISO: CONNECTION1.MISO, U$4.GPIO19
MODE1: IM1.IO17, U$12.R
MOSI: CONNECTION1.MOSI, U$4.GPIO23, U$14.E
unnamed: U$1.SOURCE, U$5.SOURCE, U$7.E
unnamed: U$5.GATE, U$7.R, U$8.A
unnamed: CONNECTOR2.1, U$1.DRAIN
unnamed: IM1.IO21, U$13.R
RF: CONNECTOR1.1, U$15.OUT1
RL: CONNECTOR1.2, U$15.OUT2
SCK: CONNECTION1.CLK, U$4.GPIO18
SCL: BMP1.P3, BMX1.SCL, U$4.GPIO22
SDA: BMP1.P4, BMX1.SDA, U$4.GPIO21
SERVOL: U$4.GPIO25, U$9.PWM, U$16.RIN
SERVOL2: U$4.GPIO33, U$11.PWM, U$16.FIN
SERVOR: U$2.PWM, U$4.GPIO26, U$15.FIN
SERVOR2: U$4.GPIO27, U$10.PWM, U$15.RIN
SS: CONNECTION1.CS, U$4.GPIO5
